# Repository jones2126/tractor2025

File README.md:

# Tractor2025 Project

An autonomous outdoor robot platform for farming and research applications.

## Overview

This repository contains the under development codebase for an outdoor robot platform initially built on an 18HP lawn tractor chassis. The system uses a dual-processor architecture combining low-level hardware control with high-level navigation and perception capabilities.

## System Architecture

### Key Components
- **Tractor and Main Chassis**: Cub Cadet XT1 LT42 with EFI riding mower tractor-based outdoor robot platform

#### Microcontroller Teensy 4.1 (Low-Level Control)
- JRK G2 motor controller → Linear actuator → Hydrostatic transmission
- IBT-2 motor controller for steering control with PID feedback
- Steering angle sensor (potentiometer on pin A9/pin 23)
- Wheel encoders (induction sensors) on left and right rear wheels
- NRF24 radio communication with remote control unit
- 4 Unit Relay GPIO board for safety systems

#### Primary Compute Raspberry Pi 5 (High-Level Control)
- Navigation stack (ROS 2 + Pure Pursuit algorithm)
- Dual ZED-F9P RTK GNSS receivers for precision localization and heading
- OAK camera for AprilTag localization and teleoperation
- Internet connectivity for RTK correction data
- Interface to Teensy 3.5 for hardware control

- **GPS**: RTK GNSS receivers Ardusimple ZED-F9P one for base link and one to calculate heading

- **Communication**: NRF24 radio link with custom radio controller; RPi wi-fi

- **Base Station**: Custom base station to send RTCM correction data.  See https://github.com/jones2126/tractor2025/blob/main/BridgevilleRTKBase/README.md

#### Localization System
- **Secondary**: Wheel odometry from rear wheel sensors
- **Vision**: OAK camera to be used for teleoperation in conjunction with wi-fi control

#### Remote Control
- Custom-built radio controller with:
  - 1 Teensy 3.2
  - 4 potentiometers (steering, throttle, aux controls)
  - 3 pushbuttons
  - 1 toggle switch
  - Emergency stop functionality
  - 1 NRF24 radio

## Control Systems

### Steering Control
- **Implementation**: PID-based steering control with potentiometer used for steer angle data on pin A9 (pin 23) which provides steering angle
- **Hardware**: IBT-2 motor controller driving steering motor
- **Modes**: Manual (radio control) and Auto (ROS cmd_vel integration planned)

### Transmission Control
- **Implementation**: Software defined 10-bucket speed control approach for speed transitions to mimic gear settings
- **Hardware**: JRK G2 motor controller for linear actuator control
- **Range**: Actuator is physically connected hydrostatic transmission which requires ~3" travel for full reverse to full forward. 

### Safety Systems
- **E-Stop**: Radio-controlled emergency stop with relay able to ground ignition wire to ground
- **Signal Loss Protection**: Automatic safe state when radio communication is lost either to radio control or wi-fi
- **Manual Override**: Physical e-stop button on tractor

## Teensy 4.1 Hardware Pin Assignments 

### Analog Inputs
- **A9 (Pin 23)**: Steering angle potentiometer

### Digital I/O
- **Pin 5**: IBT-2 steering motor control - Connect to IBT-2 pin 1 (RPWM)
- **Pin 6**: IBT-2 steering motor control - Connect to IBT-2 pin 2 (LPWM)
- **Pin 32**: E-stop relay control
- **Pins 9, 10**: NRF24 radio (CE, CSN)
- **Pins 13, 11, 12**: NRF24 radio SPI pins (SCK, MOSI, MISO)

### Serial Communications
- **Serial3**: JRK G2 motor controller communication - pins 7 and 8

## Radio Control Operating Modes

- **Manual**: Direct radio control operation with PID steering assistance
- **Automated**: Autonomous navigation with Pure Pursuit (in development)
- **Paused/Standby**: System idle state

## Development Environment

### Software Stack
- **Languages**: C++ (Teensy), Python (RPi)
- **Frameworks**: RPi: Ubuntu 24.04, ROS 2, PlatformIO
- **Navigation**: Pure Pursuit algorithm
- **Remote Access**: NoMachine, FileZilla, PuTTY, ZeroTier for VPN

### Development Workflow
1. Code editing on laptop using VSCode
2. Commit changes to GitHub repository
3. From Raspberry Pi 5 on tractor pull updates from GitHub 
4. Compile and upload Teensy code using PlatformIO CLI
5. Deploy and test on tractor robot platform

## Repository Structure

```
NOT ACCURATE; JUST A PLACEHOLDER
tractor2025/
├── teensy/                 # Teensy 3.5 firmware (C++)
│   ├── src/               # Source code
│   ├── lib/               # Libraries
│   └── platformio.ini     # PlatformIO configuration
├── rpi/                   # Raspberry Pi code (Python)
│   ├── src/               # Source code
│   ├── launch/            # ROS 2 launch files
│   └── config/            # Configuration files
├── docs/                  # Documentation
└── README.md             # This file
```

## Getting Started

### Prerequisites - Robot
- Raspberry Pi 5 with Ubuntu 24 and ROS 2 installed
- PlatformIO CLI for Teensy development
- RTK base station configured and operational
- GPS units, JRK G2, IBT-2, 4 port relay
- Teensy 4.1

### Prerequisites - Radio Control Unit
- Teensy 3.2
- Custom designed PCB using EasyEDA - available for sharing
- Multiple components soldered to PCB (e.g. potentiometers, RGB LEDs, switch, pushbutton, etc.)

### Getting Started
1. Join the Slack Group:
   ```bash
     Sign up for Slack access to Lawn Tractor Automation: https://app.slack.com/client/T8WP3RHH7/C8YBK20LX
   ```

2. Engage with small group:
   ```bash
    Join Zoom meeting on Thursdays at Noon (ET)) https://us02web.zoom.us/j/82088036016?pwd=K2lLc1FiWm9MU0dzRStxM2J2b3dpQT09#success
   ```

3. Review previous meetings on YouTube:
   ```bash
    Lawn Tractor Automation YouTube page:  https://www.youtube.com/@lawntractorautomation2726/videos
   ```

4. Review details on shared Miro Board:
   ```bash
    Miro board: https://miro.com/app/board/uXjVM1yzdFo=/
   ```

## Safety Features
- Emergency stop via radio controller with relay-based ignition kill
- Manual e-stop on tractor
- Automatic safe state on radio signal loss

## Contact
[aej2126 _at_ protonmail !dot! com]

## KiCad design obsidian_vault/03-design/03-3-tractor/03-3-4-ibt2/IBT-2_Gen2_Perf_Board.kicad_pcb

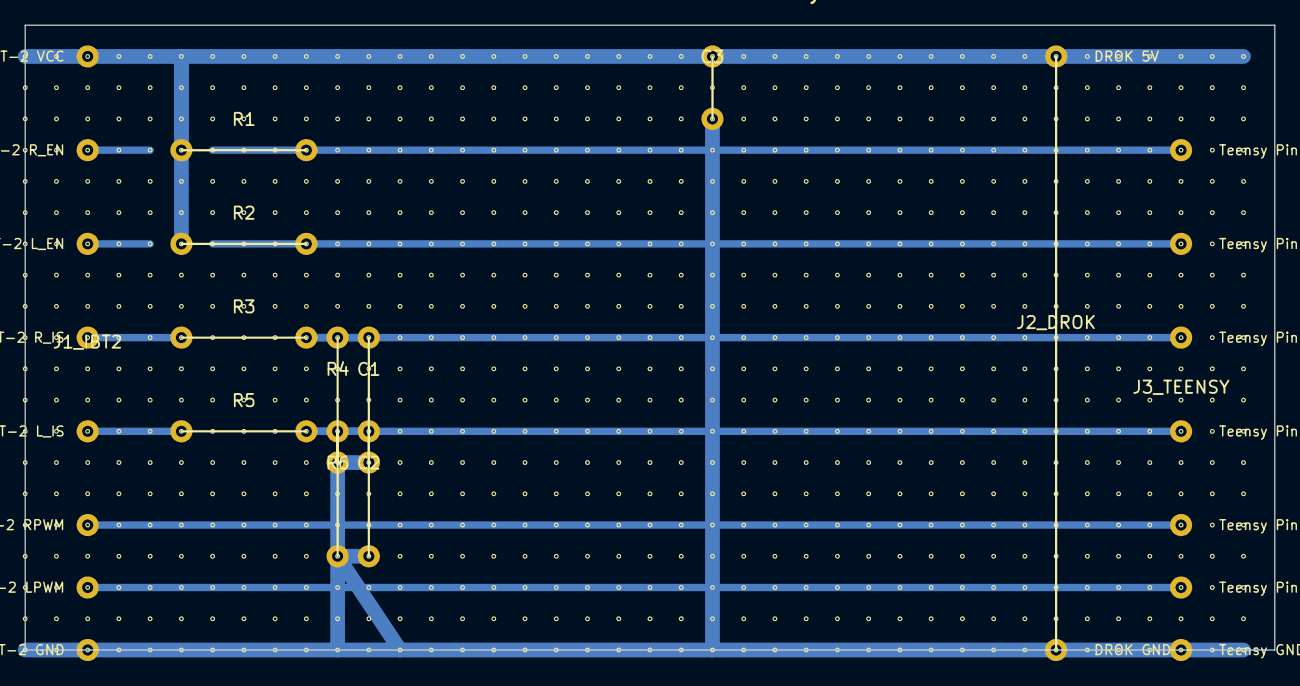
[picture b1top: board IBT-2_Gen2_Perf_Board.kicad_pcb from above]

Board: 2 copper layers, 101.6 x 50.8 mm, 12 parts (0 on the bottom side), 10 nets.

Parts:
C1, C2: 100nF; cap
C3: 100uF 16V; ecap
J1_IBT2, J2_DROK, J3_TEENSY: wire/header pads; wire_pads
R1, R2, R3, R4, R5, R6: 10k; resistor

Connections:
5V: C3.1, J1_IBT2.1, J2_DROK.1, R1.1, R2.1
GND: C1.2, C2.2, C3.2, J1_IBT2.8, J2_DROK.2, J3_TEENSY.7, R4.2, R6.2
LPWM: J1_IBT2.7, J3_TEENSY.6
L_EN_NODE: J1_IBT2.3, J3_TEENSY.2, R2.2
L_IS_IN: J1_IBT2.5, R5.1
L_IS_MID: C2.1, J3_TEENSY.4, R5.2, R6.1
RPWM: J1_IBT2.6, J3_TEENSY.5
R_EN_NODE: J1_IBT2.2, J3_TEENSY.1, R1.2
R_IS_IN: J1_IBT2.4, R3.1
R_IS_MID: C1.1, J3_TEENSY.3, R3.2, R4.1

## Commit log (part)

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2026-06-09 20260609: JRK transmission calibration complete - neutral=2836, forward=2288, reverse=3138
2026-06-11 Update mode switch values to match teensy case statements
2026-06-14 Add install_repo_sync.sh; move setup docs from obsidian to tractor_rpi/setup/
2026-06-14 Reorganize: move test files to testing/, remove old rtcm_server_20251220.py
2026-06-14 Fix production filenames in project-overview; add firmware_versions.md
2026-06-14 RC handheld firmware 20260612: checkModeSW fix, pin renames; update firmware_versions
2026-06-15 Fix install_repo_sync.sh: auto-detect repo path from script location
2026-06-15 fix repo_sync: handle ahead/diverged cases; avoid false UPDATED on local-only commits
2026-06-17 Update rtcm_server to 20260617 with VTG ground speed parsing; update install_services.sh and docs
2026-06-17 Added script to capture UDP 6002 and 6003 data for field testing
2026-06-17 Add systemd service files to setup folder for reference and tractor02 deployment
2026-06-17 Fix e-stop relay pin 32->30, confirmed IN2 on relay board
2026-06-17 updated firmware.md
2026-06-18 tractor02 setup: X20D udev rule, rtcm_server_x20d_20260617, service files with -u flag
2026-06-20 tractor02 setup improvements
2026-06-21 install_repo_sync: add richer dirty/ahead reporting with filenames and commit messages, update milestones
2026-06-21 update firmware.md with cleaner file list
2026-06-22 Update setup docs and ethernet phase4 testing
2026-06-22 Add .pio/ to .gitignore
2026-06-22 changes based on new .gitignore
2026-06-22 Add *.bak to .gitignore
2026-06-23 field_test_logger: add GPS-only mode when Teensy bridge absent, fix SO_REUSEPORT
2026-06-23 Replace esp32 downloader with version supporting status/download/download_delete commands
2026-06-24 Add boot-time ESP32 timesync, updated downloader, firmware with logging guard
2026-06-24 Restructure repo: BridgevilleRTKBase -> RTKBase with Bridgeville/Brenham/testing/setup folders
2026-06-24 Add Bridgeville RTK base station setup and rebuild guide
2026-06-24 Add WiFi RSSI monitor service for rtkbase
2026-06-24 Rename rtcm_base_server to 20260624, fix service file path
2026-06-24 Gitignore runtime data files on rtkbase
2026-06-24 Fix rtcm_server path, add logger_setup, add current_position.json to gitignore
2026-06-24 Update setup-Bridgeville.md for 20260624 changes
2026-06-27 Update RTK base Wi-Fi monitor
2026-06-27 Add RTK base survey and diagnostic tools
2026-06-27 Add Teensy serial bridge and UDP broadcast test
2026-06-28 Stop tracking RTK daily position log
2026-06-28 Add F9P survey setup utility
2026-06-28 Move daily_esp32_download.sh into repo under RTKBase/Bridgeville
2026-06-28 Update setup doc: daily_esp32_download.sh now in repo
2026-06-28 Fix SCRIPT_DIR path in daily_esp32_download.sh after repo restructure
2026-06-28 fix: RTCM buffer desync on incomplete messages - add incomplete_message flag and break
2026-06-29 Add teensy_serial_bridge_20260625: fix UDP broadcast to ZeroTier interface (192.168.193.255)
2026-06-29 Rename teensy_serial_bridge_20260625-h.py to teensy_serial_bridge_20260625.py: fix UDP broadcast to ZeroTier interface
2026-06-29 Add SkyTraq RTK base survey workflow; remove rtcm_base_server_20260624
2026-06-29 Update PORT to /dev/skytraq in SkyTraq survey and commit scripts
2026-06-29 Increase COMMAND_RESPONSE_SECONDS 2.5->8.0 to handle RTCM traffic delay
2026-06-29 Ignore SkyTraq survey candidate JSON files in RTKBase/setup
2026-06-29 Fix UDP_BIND_IP for tractor01 ZeroTier address (193.76)
